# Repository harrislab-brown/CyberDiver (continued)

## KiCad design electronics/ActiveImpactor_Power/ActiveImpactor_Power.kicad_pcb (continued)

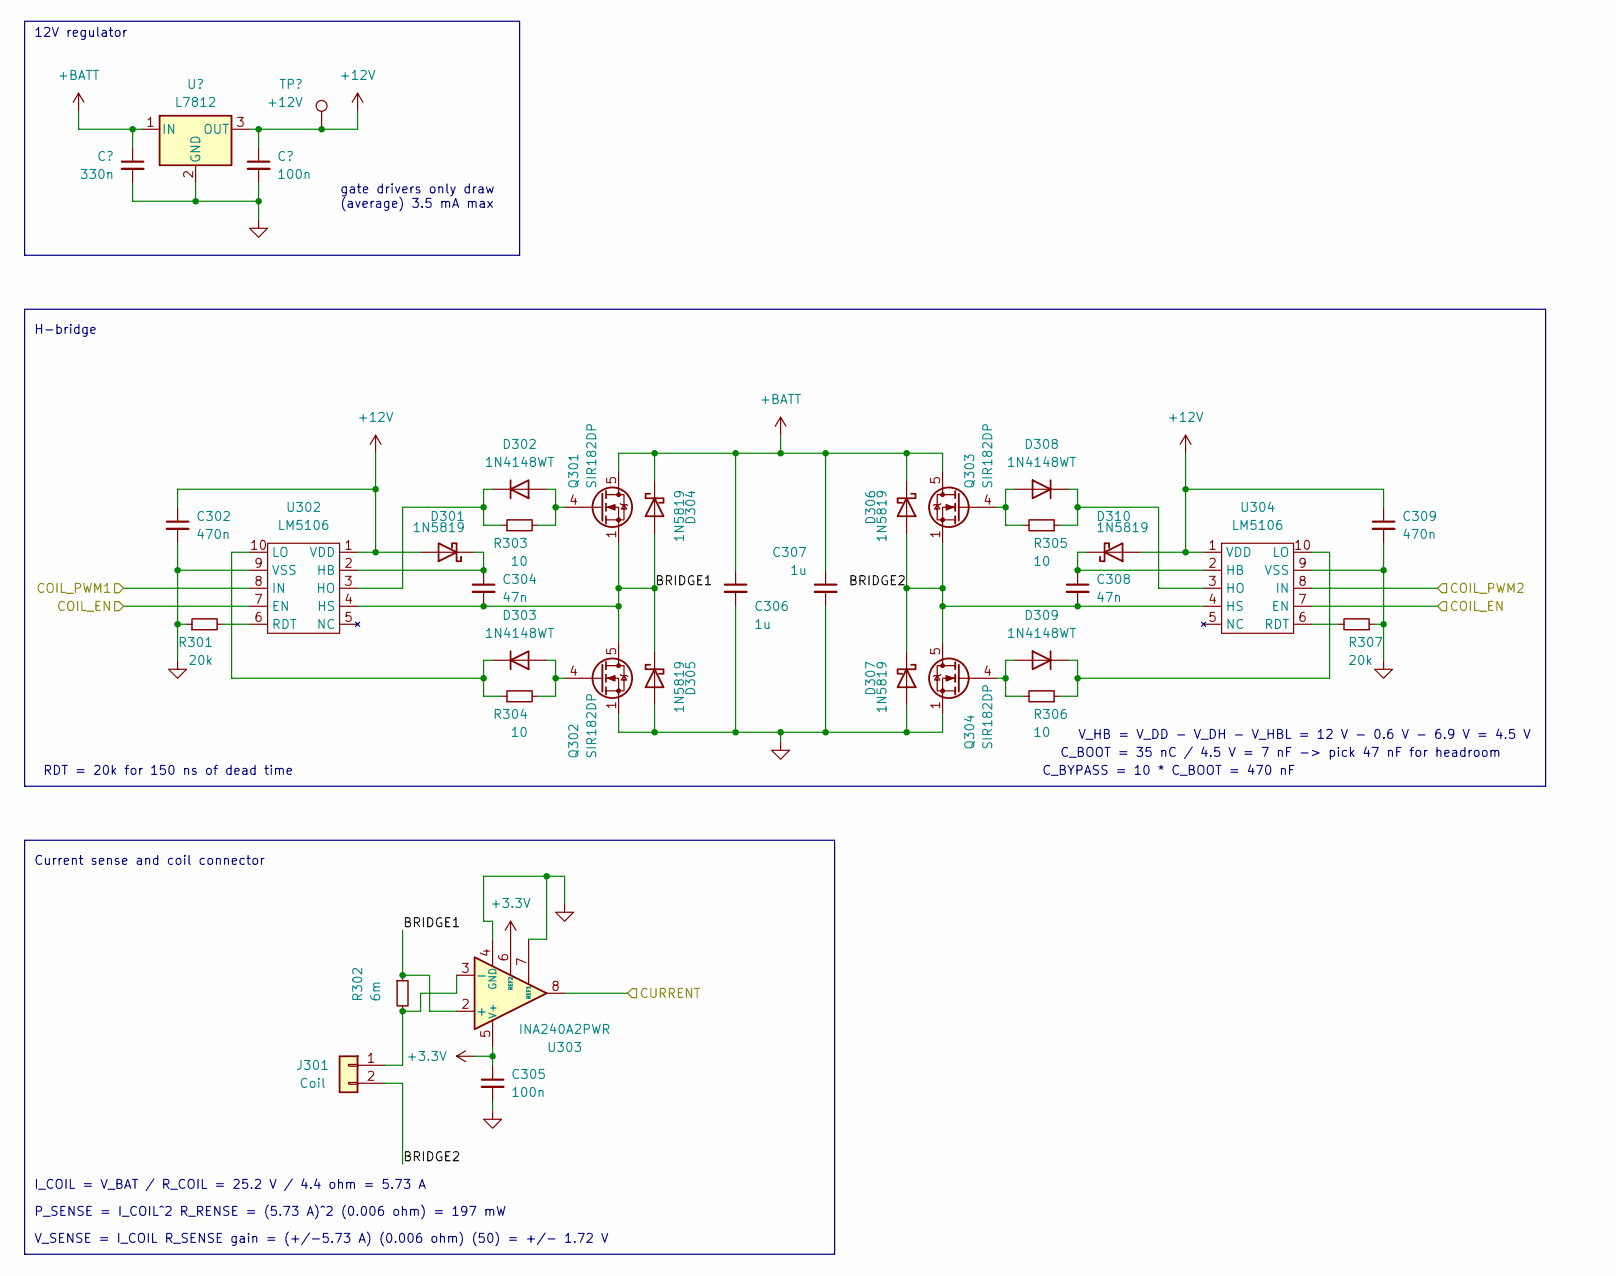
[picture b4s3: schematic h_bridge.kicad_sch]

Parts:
C301: 330n; C_0603_1608Metric; LCSC C188679
C302, C309: 470n; C_0402_1005Metric; LCSC C437527
C303, C305: 100n; C_0603_1608Metric; LCSC C14663
C304, C308: 47n; C_0402_1005Metric; LCSC C880605
C306, C307: 1u; C_1206_3216Metric; LCSC C1848
D301, D304, D305, D306, D307, D310: 1N5819; D_SOD-523; LCSC C5451630
D302, D303, D308, D309: 1N4148WT; D_SOD-523; LCSC C727112
J301: Coil; JST_PH_S2B-PH-SM4-TB_1x02-1MP_P2.00mm_Horizontal; LCSC C295747
Q301, Q302, Q303, Q304: SIR182DP; PowerPAK_SO-8_Single; LCSC C467943
R301, R307: 20k; R_0402_1005Metric; LCSC C25765
R302: 6m; R_2512_6332Metric; LCSC C2985709
R303, R304, R305, R306: 10; R_0402_1005Metric; LCSC C25077
TP301: +12V; TestPoint_Pad_D1.0mm
U301: L7812; TO-252-2; LCSC C16424
U302, U304: LM5106; VSSOP-10_3x3mm_P0.5mm; LCSC C91879
U303: INA240A2PWR; TSSOP-8_4.4x3mm_P0.65mm; LCSC C129949

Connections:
+3.3V: C305.1, U303.5 (V+), U303.6 (REF2); also elsewhere on the board
+12V: C302.1, C303.1, C309.1, D301.2 (A), D310.2 (A), TP301.1, U301.3 (OUT), U302.1 (VDD), U304.1 (VDD)
+BATT: C301.1, C306.1, C307.1, D304.1 (K), D306.1 (K), Q301.5 (D), Q303.5 (D), U301.1 (IN); also elsewhere on the board
/H-Bridge/BRIDGE1: C304.2, D304.2 (A), D305.1 (K), Q301.1 (S), Q301.2 (S), Q301.3 (S), Q302.5 (D), R302.1, U302.4 (HS), U303.2 (+)
/H-Bridge/BRIDGE2: C308.2, D306.2 (A), D307.1 (K), J301.2, Q303.1 (S), Q303.2 (S), Q303.3 (S), Q304.5 (D), U304.4 (HS)
/H-Bridge/COIL_EN: U302.7 (EN), U304.7 (EN); also elsewhere on the board
/H-Bridge/COIL_PWM1: U302.8 (IN); also elsewhere on the board
/H-Bridge/COIL_PWM2: U304.8 (IN); also elsewhere on the board
/H-Bridge/CURRENT: U303.8; also elsewhere on the board
GND: C301.2, C302.2, C303.2, C305.2, C306.2, C307.2, C309.2, D305.2 (A), D307.2 (A), Q302.1 (S), Q302.2 (S), Q302.3 (S), Q304.1 (S), Q304.2 (S), Q304.3 (S), R301.1, R307.1, U301.2 (GND), U302.9 (VSS), U303.1 (GND), U303.4 (GND), U303.7 (REF1), U304.9 (VSS); also elsewhere on the board
unnamed: C304.1, D301.1 (K), U302.2 (HB)
unnamed: D302.2 (A), Q301.4 (G), R303.2
unnamed: D302.1 (K), R303.1, U302.3 (HO)
unnamed: D303.2 (A), Q302.4 (G), R304.2
unnamed: D303.1 (K), R304.1, U302.10 (LO)
unnamed: D308.2 (A), Q303.4 (G), R305.2
unnamed: D308.1 (K), R305.1, U304.3 (HO)
unnamed: D309.2 (A), Q304.4 (G), R306.2
unnamed: D309.1 (K), R306.1, U304.10 (LO)
unnamed: C308.1, D310.1 (K), U304.2 (HB)
unnamed: J301.1, R302.2, U303.3 (-)
unnamed: R301.2, U302.6 (RDT)
unnamed: R307.2, U304.6 (RDT)

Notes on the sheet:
H-bridge
C_BYPASS = 10 * C_BOOT = 470 nF
gate drivers only draw (average) 3.5 mA max
V_HB = V_DD - V_DH - V_HBL = 12 V - 0.6 V - 6.9 V = 4.5 V
12V regulator
RDT = 20k for 150 ns of dead time
C_BOOT = 35 nC / 4.5 V = 7 nF -> pick 47 nF for headroom
P_SENSE = I_COIL^2 R_RENSE = (5.73 A)^2 (0.006 ohm) = 197 mW
V_SENSE = I_COIL R_SENSE gain = (+/-5.73 A) (0.006 ohm) (50) = +/- 1.72 V
I_COIL = V_BAT / R_COIL = 25.2 V / 4.4 ohm = 5.73 A
Current sense and coil connector

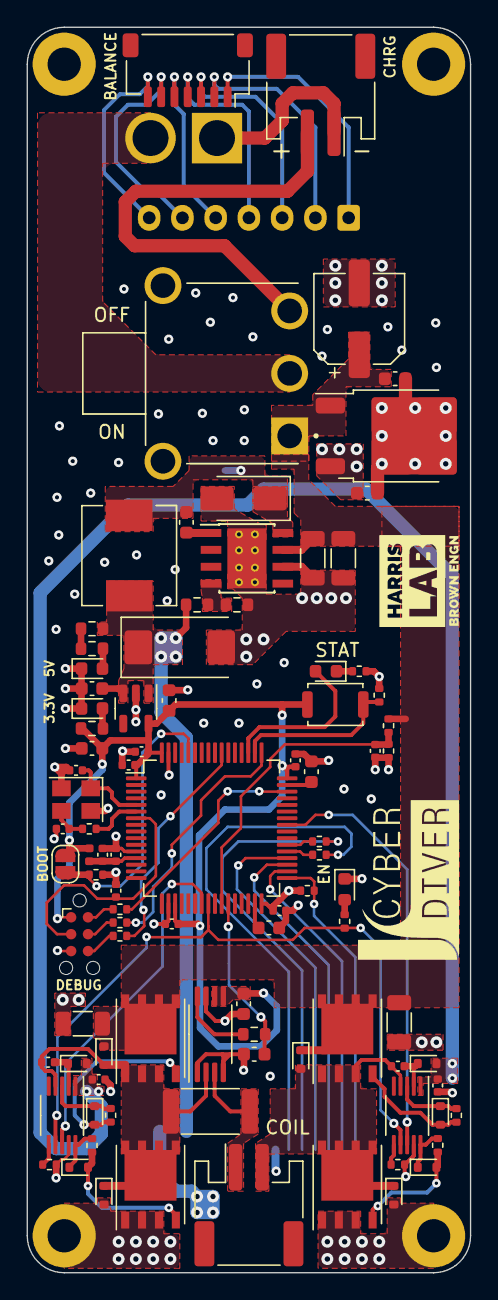
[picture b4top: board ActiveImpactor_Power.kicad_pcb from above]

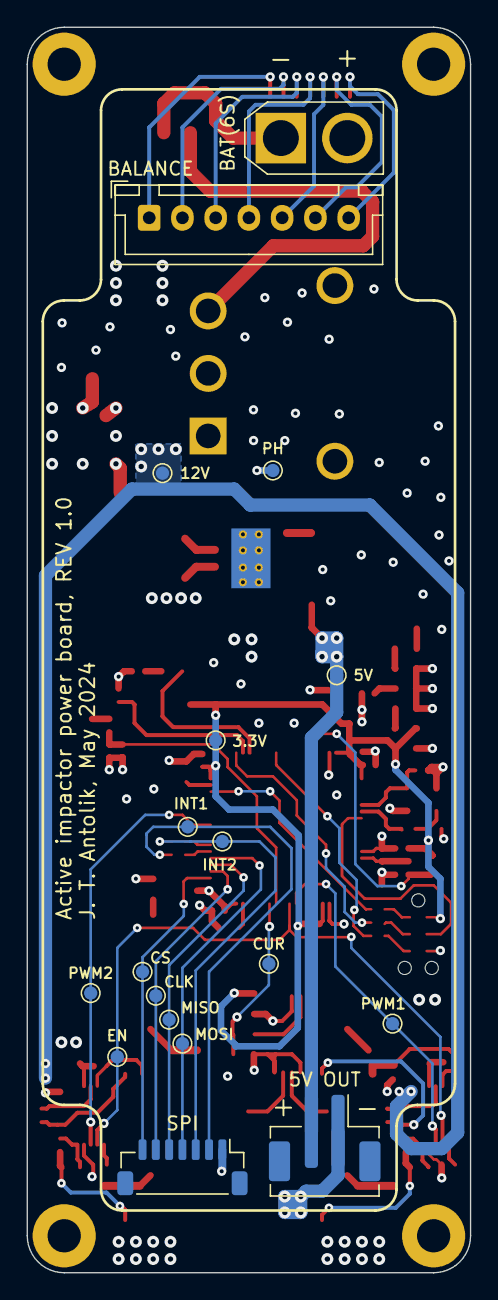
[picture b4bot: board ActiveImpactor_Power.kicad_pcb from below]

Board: 4 copper layers, 33.3 x 93.7 mm, 115 parts (18 on the bottom side), 67 nets.

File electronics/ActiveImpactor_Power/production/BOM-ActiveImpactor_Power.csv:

Comment,Designator,Footprint,LCSC
TLV70033_SOT23-5,U102,SOT-23-5,C11337
1k,"R109,R111,R201",R_0402_1005Metric,C11702
100u,C101,CP_Elec_6.3x5.8,C128464
INA240A2PWR,U303,TSSOP-8_4.4x3mm_P0.65mm,C129949
16MHz,Y201,Crystal_SMD_3225-4Pin_3.2x2.5mm,C13738
7k5,R108,R_0402_1005Metric,C137934
100n,"C303,C305",C_0603_1608Metric,C14663
10n,"C106,C210",C_0402_1005Metric,C15195
100n,"C202,C205,C206,C207,C208,C212",C_0402_1005Metric,C1525
12p,"C211,C213",C_0402_1005Metric,C1547
STM32F405RGT6,U201,LQFP-64_10x10mm_P0.5mm,C15742
Balance,J104,JST_SH_SM07B-SRSS-TB_1x07-1MP_P1.00mm_Horizontal,C160406
L7812,U301,TO-252-2,C16424
1u,"C306,C307",C_1206_3216Metric,C1848
330n,C301,C_0603_1608Metric,C188679
4u7,"C108,C109",C_0603_1608Metric,C19666
10u,C201,C_0603_1608Metric,C19702
BUTTON,SW201,SW_Push_SPST_NO_Alps_SKRK,C202388
1k,"R106,R107,R110,R112",R_0603_1608Metric,C21190
LED_EN,D103,LED_0603_1608Metric,C2286
3.24k,R105,R_0603_1608Metric,C22994
2u2,"C203,C204",C_0603_1608Metric,C23630
220u,C105,CP_EIA-7343-40_Kemet-Y,C242173
10,"R303,R304,R305,R306",R_0402_1005Metric,C25077
22,"R102,R103,R205,R206,R207",R_0402_1005Metric,C25092
47,R204,R_0402_1005Metric,C25118
10k,"R202,R203",R_0402_1005Metric,C25744
20k,"R301,R307",R_0402_1005Metric,C25765
47k,R101,R_0402_1005Metric,C25792
10k,R104,R_0603_1608Metric,C25804
39n,L201,L_0402_1005Metric,C26443
Charge,"J105,J301",JST_PH_S2B-PH-SM4-TB_1x02-1MP_P2.00mm_Horizontal,C295747
4.7u,"C102,C103",C_1206_3216Metric,C29823
6m,R302,R_2512_6332Metric,C2985709
22u,L101,L_Sunlord_MWSA0603S,C408453
470n,"C302,C309",C_0402_1005Metric,C437527
SIR182DP,"Q301,Q302,Q303,Q304",PowerPAK_SO-8_Single,C467943
1u,C209,C_0402_1005Metric,C52923
4.7n,C107,C_0603_1608Metric,C53987
1N5819,"D301,D304,D305,D306,D307,D310",D_SOD-523,C5451630
10n,C104,C_0603_1608Metric,C57112
B340,D101,D_SMA,C64982
1N4148WT,"D302,D303,D308,D309",D_SOD-523,C727112
STAT,D201,LED_0603_1608Metric,C84266
47n,"C304,C308",C_0402_1005Metric,C880605
LM5106,"U302,U304",VSSOP-10_3x3mm_P0.5mm,C91879
LED_5V,"D102,D104",LED_0603_1608Metric,C965805
TPS5430DDA,U101,TI_SO-PowerPAD-8_ThermalVias,C9864

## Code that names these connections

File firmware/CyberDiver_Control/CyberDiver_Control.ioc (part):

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Mcu.Name=STM32H723ZGTx
Mcu.Package=LQFP144
Mcu.UserName=STM32H723ZGTx
PA0.Signal=S_TIM2_CH1_ETR
PA1.Signal=S_TIM2_CH2
PA11.Mode=Device_Only_FS
PA11.Signal=USB_OTG_HS_DM
PA12.Mode=Device_Only_FS
PA12.Signal=USB_OTG_HS_DP
PA13(JTMS/SWDIO).Mode=Trace_Asynchronous_SW
PA13(JTMS/SWDIO).Signal=DEBUG_JTMS-SWDIO
PA14(JTCK/SWCLK).Mode=Trace_Asynchronous_SW
PA14(JTCK/SWCLK).Signal=DEBUG_JTCK-SWCLK
PA2.GPIOParameters=GPIO_Label
PA2.GPIO_Label=ENC_IW
PA2.Signal=GPIO_Input
PA4.GPIOParameters=GPIO_Speed,PinState,GPIO_Label
PA4.GPIO_Label=SPI6_NSS
PA4.GPIO_Speed=GPIO_SPEED_FREQ_VERY_HIGH
PA4.PinState=GPIO_PIN_SET
PA4.Signal=GPIO_Output
PA5.Mode=Full_Duplex_Master
PA5.Signal=SPI6_SCK
PA6.Mode=Full_Duplex_Master
PA6.Signal=SPI6_MISO
PA7.Mode=Full_Duplex_Master
PA7.Signal=SPI6_MOSI
PB12.Mode=NSS_Signal_Hard_Output
PB12.Signal=SPI2_NSS
PB13.Mode=Full_Duplex_Master
PB13.Signal=SPI2_SCK
PB14.Mode=Full_Duplex_Master
PB14.Signal=SPI2_MISO
PB15.Mode=Full_Duplex_Master
PB15.Signal=SPI2_MOSI
PB3(JTDO/TRACESWO).Mode=Trace_Asynchronous_SW
PB3(JTDO/TRACESWO).Signal=DEBUG_JTDO-SWO
PB4(NJTRST).GPIOParameters=GPIO_Label
PB4(NJTRST).GPIO_Label=IIS3DWB_INT1
PB4(NJTRST).Signal=GPXTI4
PB5.GPIOParameters=GPIO_Label
PB5.GPIO_Label=IIS3DWB_INT2
PB5.Signal=GPIO_Input
PB6.GPIOParameters=GPIO_Label
PB6.GPIO_Label=ADXL372_INT1
PB6.Signal=GPIO_Input
PB7.GPIOParameters=GPIO_Label
PB7.GPIO_Label=ADXL372_INT2
PB7.Signal=GPIO_Input
PB8.GPIOParameters=GPIO_Label
PB8.GPIO_Label=LSM6DS3_INT1
PB8.Signal=GPIO_Input
PB9.GPIOParameters=GPIO_Label
PB9.GPIO_Label=LSM6DS3_INT2
PB9.Signal=GPIO_Input
PC0.Signal=FMC_SDNWE
PC10.Mode=SD_4_bits_Wide_bus
PC10.Signal=SDMMC1_D2
PC11.Mode=SD_4_bits_Wide_bus
PC11.Signal=SDMMC1_D3
PC12.Mode=SD_4_bits_Wide_bus
PC12.Signal=SDMMC1_CK
PC14-OSC32_IN.GPIOParameters=GPIO_Label
PC14-OSC32_IN.GPIO_Label=LED_STATUS
PC14-OSC32_IN.Signal=GPIO_Output
PC15-OSC32_OUT.GPIOParameters=GPIO_Label
PC15-OSC32_OUT.GPIO_Label=BUTTON
PC15-OSC32_OUT.Signal=GPIO_Input
PC2_C.Mode=SdramChipSelect1_1
PC2_C.Signal=FMC_SDNE0
PC3_C.Mode=SdramChipSelect1_1
PC3_C.Signal=FMC_SDCKE0
PC8.Mode=SD_4_bits_Wide_bus
PC8.Signal=SDMMC1_D0
PC9.Mode=SD_4_bits_Wide_bus
PC9.Signal=SDMMC1_D1
PD0.Signal=FMC_D2_DA2
PD1.Signal=FMC_D3_DA3
PD10.Signal=FMC_D15_DA15
PD11.GPIOParameters=GPIO_Label
PD11.GPIO_Label=SD_DET
PD11.Signal=GPIO_Input
PD14.Signal=FMC_D0_DA0
PD15.Signal=FMC_D1_DA1
PD2.Mode=SD_4_bits_Wide_bus
PD2.Signal=SDMMC1_CMD
PD4.GPIOParameters=GPIO_Label
PD4.GPIO_Label=PWR_INT2
PD4.Signal=GPIO_Input
PD5.GPIOParameters=GPIO_Speed,GPIO_Label
PD5.GPIO_Label=PWR_INT1
PD5.GPIO_Speed=GPIO_SPEED_FREQ_VERY_HIGH
PD5.Signal=GPIO_Output
PD7.Mode=Full_Duplex_Master
PD7.Signal=SPI1_MOSI
PD8.Signal=FMC_D13_DA13
PD9.Signal=FMC_D14_DA14
PE0.Signal=FMC_NBL0
PE1.Signal=FMC_NBL1
PE10.Signal=FMC_D7_DA7
PE11.Signal=FMC_D8_DA8
PE12.Signal=FMC_D9_DA9
PE13.Signal=FMC_D10_DA10
PE14.Signal=FMC_D11_DA11
PE15.Signal=FMC_D12_DA12
PE2.Mode=Full_Duplex_Master
PE2.Signal=SPI4_SCK
PE3.GPIOParameters=GPIO_Label
PE3.GPIO_Label=EXP_INT
PE3.Signal=GPIO_Input
PE4.Mode=NSS_Signal_Hard_Output
PE4.Signal=SPI4_NSS
PE5.Mode=Full_Duplex_Master
PE5.Signal=SPI4_MISO
PE6.Mode=Full_Duplex_Master
PE6.Signal=SPI4_MOSI
PE7.Signal=FMC_D4_DA4
PE8.Signal=FMC_D5_DA5
PE9.Signal=FMC_D6_DA6
PF0.Signal=FMC_A0
PF1.Signal=FMC_A1
PF11.Signal=FMC_SDNRAS
PF12.Signal=FMC_A6
PF13.Signal=FMC_A7
PF14.Signal=FMC_A8
PF15.Signal=FMC_A9
PF2.Signal=FMC_A2
PF3.Signal=FMC_A3
PF4.Signal=FMC_A4
PF5.Signal=FMC_A5
PF6.Mode=NSS_Signal_Hard_Output
PF6.Signal=SPI5_NSS
PF7.Mode=Full_Duplex_Master
PF7.Signal=SPI5_SCK
PF8.Mode=Full_Duplex_Master
PF8.Signal=SPI5_MISO
PF9.Mode=Full_Duplex_Master
PF9.Signal=SPI5_MOSI
PG0.Signal=FMC_A10
PG1.Signal=FMC_A11
PG10.GPIOParameters=GPIO_Speed,PinState,GPIO_Label
PG10.GPIO_Label=SPI1_NSS
PG10.GPIO_Speed=GPIO_SPEED_FREQ_VERY_HIGH
PG10.PinState=GPIO_PIN_SET
PG10.Signal=GPIO_Output
PG11.Mode=Full_Duplex_Master
PG11.Signal=SPI1_SCK
PG15.Signal=FMC_SDNCAS
PG4.Signal=FMC_A14_BA0
PG5.Signal=FMC_A15_BA1
PG8.Signal=FMC_SDCLK
PG9.Mode=Full_Duplex_Master
PG9.Signal=SPI1_MISO
PH0-OSC_IN.Mode=HSE-External-Oscillator
PH0-OSC_IN.Signal=RCC_OSC_IN
PH1-OSC_OUT.Mode=HSE-External-Oscillator
PH1-OSC_OUT.Signal=RCC_OSC_OUT
RCC.HSE_VALUE=24000000
RCC.SYSCLKFreq_VALUE=550000000
RCC.SYSCLKSource=RCC_SYSCLKSOURCE_PLLCLK
board=custom

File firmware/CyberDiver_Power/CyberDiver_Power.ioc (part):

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Mcu.Name=STM32F405RGTx
Mcu.Package=LQFP64
Mcu.UserName=STM32F405RGTx
PA13.Mode=Trace_Asynchronous_SW
PA13.Signal=SYS_JTMS-SWDIO
PA14.Mode=Trace_Asynchronous_SW
PA14.Signal=SYS_JTCK-SWCLK
PA15.GPIOParameters=GPIO_Label
PA15.GPIO_Label=BUTTON
PA15.Signal=GPIO_Input
PA7.GPIOParameters=GPIO_Label
PA7.GPIO_Label=COIL_PWM1
PA7.Signal=S_TIM3_CH2
PA8.GPIOParameters=GPIO_Label
PA8.GPIO_Label=COIL_PWM2
PA8.Signal=S_TIM1_CH1
PB0.GPIOParameters=GPIO_Label
PB0.GPIO_Label=ADC_VBAT
PB0.Signal=ADCx_IN8
PB1.GPIOParameters=GPIO_Label
PB1.GPIO_Label=ADC_CURRENT
PB1.Signal=ADCx_IN9
PB12.Mode=NSS_Signal_Hard_Input
PB12.Signal=SPI2_NSS
PB13.Mode=Full_Duplex_Slave
PB13.Signal=SPI2_SCK
PB14.Mode=Full_Duplex_Slave
PB14.Signal=SPI2_MISO
PB15.Mode=Full_Duplex_Slave
PB15.Signal=SPI2_MOSI
PB3.Mode=Trace_Asynchronous_SW
PB3.Signal=SYS_JTDO-SWO
PC10.GPIOParameters=GPIO_Label
PC10.GPIO_Label=LED_STATUS
PC10.Signal=GPIO_Output
PC4.GPIOParameters=GPIO_Speed,GPIO_Label
PC4.GPIO_Label=COIL_EN
PC4.GPIO_Speed=GPIO_SPEED_FREQ_VERY_HIGH
PC4.Signal=GPIO_Output
PC6.GPIOParameters=GPIO_Label,GPIO_ModeDefaultEXTI
PC6.GPIO_Label=PWR_INT1
PC6.GPIO_ModeDefaultEXTI=GPIO_MODE_IT_RISING_FALLING
PC6.Signal=GPXTI6
PC7.GPIOParameters=GPIO_Speed,GPIO_Label
PC7.GPIO_Label=PWR_INT2
PC7.GPIO_Speed=GPIO_SPEED_FREQ_VERY_HIGH
PC7.Signal=GPIO_Output
PH0-OSC_IN.Mode=HSE-External-Oscillator
PH0-OSC_IN.Signal=RCC_OSC_IN
PH1-OSC_OUT.Mode=HSE-External-Oscillator
PH1-OSC_OUT.Signal=RCC_OSC_OUT
RCC.HSE_VALUE=16000000
RCC.SYSCLKFreq_VALUE=168000000
RCC.SYSCLKSource=RCC_SYSCLKSOURCE_PLLCLK
board=custom

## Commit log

2025-03-15 added board designs
2025-03-15 added firmware
2025-03-15 added mechanical design
2025-03-16 added schematics and flexure scripts
2025-03-16 added assets and raw data files
2025-03-16 added csvs with aggregate data
2025-03-16 added matlab scripts
2025-03-16 added movies
2025-03-17 swapped movies s4 and s5 to be consistent with paper
